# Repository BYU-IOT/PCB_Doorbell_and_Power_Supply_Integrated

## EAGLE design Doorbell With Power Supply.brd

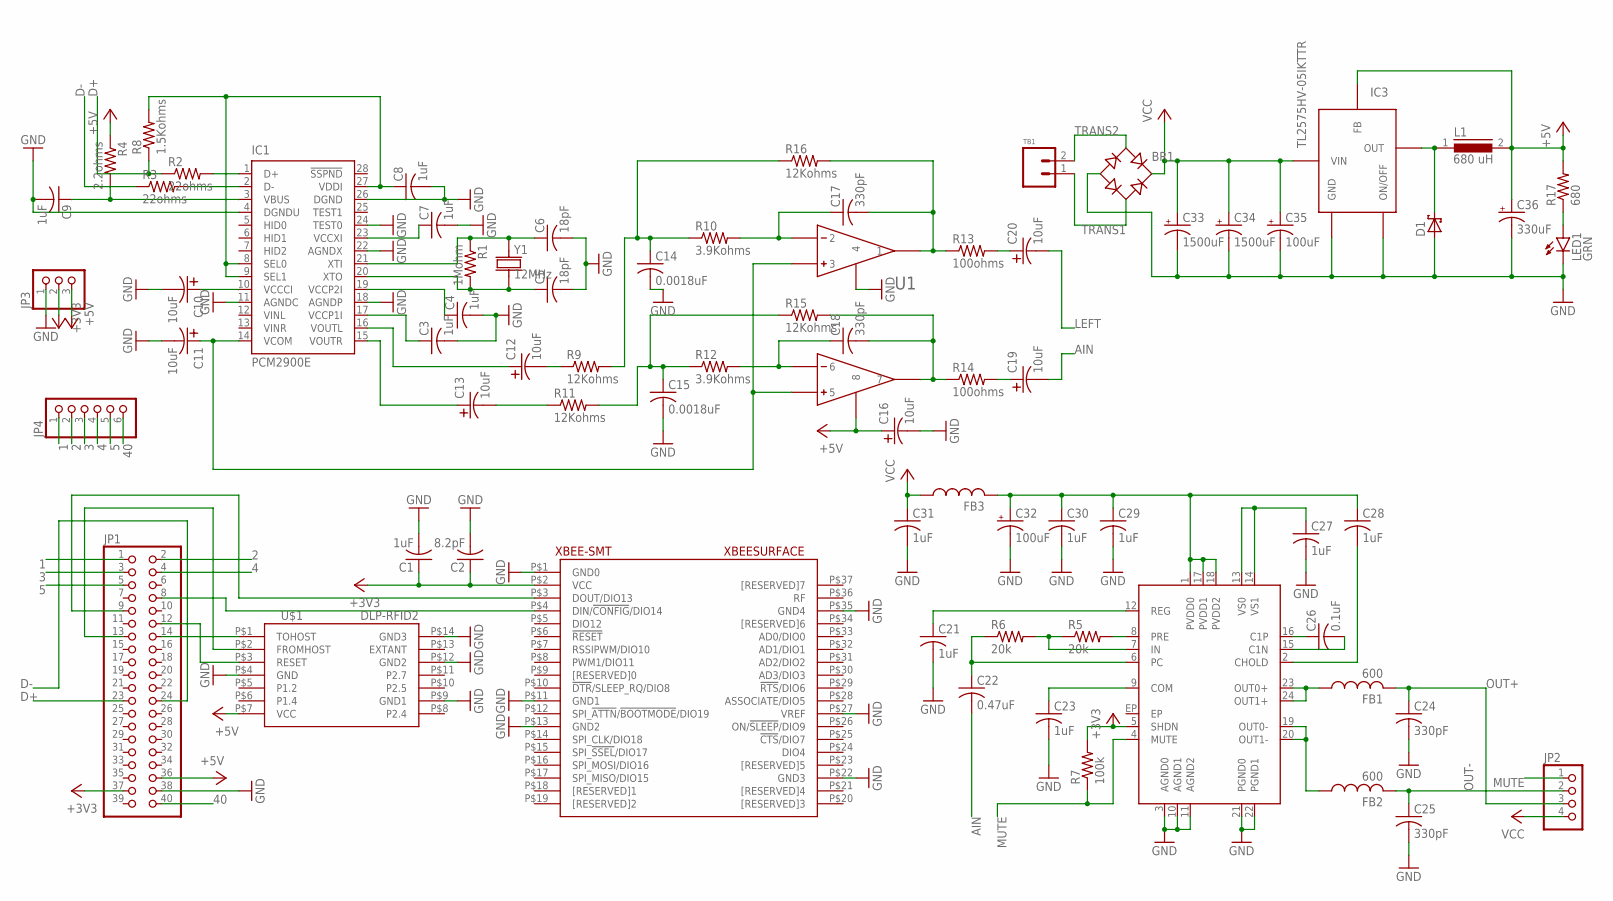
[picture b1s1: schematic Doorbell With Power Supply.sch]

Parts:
BR1: BR; DFS
C1, C3, C4, C7, C8, C9, C21, C23, C27, C28, C29, C30, C31: 1uF; 0603_CAP
C2: 8.2pF; 0603_CAP
C5, C6: 18pF; 0603_CAP
C10, C11, C12, C13, C16, C19, C20: 10uF; 1411_CAP
C14, C15: 0.0018uF; 0603_CAP
C17, C18, C24, C25: 330pF; 0603_CAP
C22: 0.47uF; 0603_CAP
C26: 0.1uF; 0603_CAP
C32, C35: 100uF; F_CAP
C33, C34: 1500uF; J16_CAP
C36: 330uF; F_CAP
D1: SCHOTTKY_DIODE; SMD_DIODE
FB1, FB2: 600; 0805_FB
FB3: FB0805; 0805_FB
IC1: PCM2900E; SSOP28DB
IC2: MAX9737; TQFN24
IC3: TL2575HV-05IKTTR; TO-263-5
JP1: PINHD-2X20; 2X20
JP2: PINHD-1X4; 1X04
JP3: PINHD-1X3; 1X03
JP4: PINHD-1X6; 1X06
L1: 680 uH; DR125
LED1: GRN; 0603_LED
R1: 1Mohm; 0603_RESISTOR
R2, R3: 22ohms; 0603_RESISTOR
R4: 2.2ohms; 0603_RESISTOR
R5, R6: 20k; 0603_RESISTOR
R7: 100k; 0603_RESISTOR
R8: 1.5Kohms; 0603_RESISTOR
R9, R11, R15, R16: 12Kohms; 0603_RESISTOR
R10, R12: 3.9Kohms; 0603_RESISTOR
R13, R14: 100ohms; 0603_RESISTOR
R17: 680; 0603_RESISTOR
TB1: TERMINAL_BLOCK_2
U1: OP-AMP; OPA2353UA
U$1: DLP-RFID2
XBEE-SMT: XBEESURFACE
Y1: 12MHz; CRYSTAL_5X3

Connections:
1: JP1.1, JP4.1
2: JP1.2, JP4.2
3: JP1.3, JP4.3
4: JP1.4, JP4.4
5: JP1.5, JP4.5
40: JP1.40, JP4.6
+3V3: C1.1, C2.1, IC2.5 (SHDN), JP1.37, JP3.2, R7.2, XBEE-SMT.P$2 (VCC)
+5V: C16.P$1, C36.+, IC3.4 (FB), JP1.36, JP3.3, L1.2, R4.1, R17.2, U1.P$8 (8), U$1.P$7 (VCC)
AIN: C19.P$2, C22.2
D+: JP1.23, R2.1, R8.1
D-: JP1.24, R3.1
GND: BR1.-, C1.2, C2.2, C3.2, C4.2, C5.2, C6.2, C7.2, C8.2, C9.2, C10.P$2, C11.P$2, C14.2, C15.2, C16.P$2, C21.2, C23.2, C24.2, C25.2, C27.2, C29.2, C30.2, C31.2, C32.-, C33.-, C34.-, C35.-, C36.-, D1.A, IC1.4 (DGNDU), IC1.11 (AGNDC), IC1.18 (AGNDP), IC1.22 (AGNDX), IC1.24 (TEST0), IC1.26 (DGND), IC2.3 (AGND0), IC2.10 (AGND1), IC2.11 (AGND2), IC2.21 (PGND0), IC2.22 (PGND1), IC3.3 (GND), IC3.5 (ON/OFF), JP1.38, JP3.1, LED1.C, U1.P$4 (4), U$1.P$4 (GND), U$1.P$9 (GND1), U$1.P$12 (GND2), U$1.P$14 (GND3), XBEE-SMT.P$1 (GND0), XBEE-SMT.P$11 (GND1), XBEE-SMT.P$13 (GND2), XBEE-SMT.P$22 (GND3), XBEE-SMT.P$27 (VREF), XBEE-SMT.P$35 (GND4)
LEFT: C20.P$2
MUTE: IC2.4 (MUTE), JP2.1, R7.1
unnamed: JP1.14, U$1.P$1 (TOHOST)
unnamed: IC2.8 (PRE), R5.2
unnamed: IC2.7 (IN), R5.1, R6.2
unnamed: JP1.12, U$1.P$3 (RESET)
unnamed: JP1.13, U$1.P$2 (FROMHOST)
unnamed: JP1.8, XBEE-SMT.P$4 (DIN/!CONFIG!/DIO14)
unnamed: JP1.9, XBEE-SMT.P$3 (DOUT/DIO13)
unnamed: C3.1, IC1.17 (VCCP1I)
unnamed: IC1.1 (D+), R2.2
unnamed: C22.1, IC2.6 (PC), R6.1
unnamed: C8.1, IC1.8 (SEL0), IC1.9 (SEL1), IC1.27 (VDDI), R8.2
unnamed: IC1.2 (D-), R3.2
unnamed: C21.1, IC2.12 (REG)
unnamed: C7.1, IC1.23 (VCCXI)
unnamed: C6.1, IC1.21 (XTI), R1.1, Y1.1
unnamed: C5.1, IC1.20 (XTO), R1.2, Y1.2
unnamed: C4.1, IC1.19 (VCCP2I)
unnamed: C12.P$2, R9.1
unnamed: C13.P$2, R11.1
unnamed: C17.1, R10.2, U1.P$2 (2)
unnamed: C10.P$1, IC1.10 (VCCCI)
unnamed: C11.P$1, IC1.14 (VCOM), U1.P$3 (3), U1.P$5 (5)
unnamed: C18.1, R12.2, U1.P$6 (6)
unnamed: C12.P$1, IC1.16 (VOUTL)
unnamed: C13.P$1, IC1.15 (VOUTR)
unnamed: C14.1, R9.2, R10.1, R16.1
unnamed: C15.1, R11.2, R12.1, R15.1
unnamed: C17.2, R13.1, R16.2, U1.P$1 (1)
unnamed: C18.2, R14.1, R15.2, U1.P$7 (7)
unnamed: D1.C, IC3.2 (OUT), L1.1
unnamed: C20.P$1, R13.2
unnamed: C19.P$1, R14.2
unnamed: C9.1, IC1.3 (VBUS), R4.2
unnamed: C23.1, IC2.9 (COM)
unnamed: LED1.A, R17.1
unnamed: FB1.1, IC2.23 (OUT0+), IC2.24 (OUT1+)
unnamed: FB2.1, IC2.19 (OUT0-), IC2.20 (OUT1-)
unnamed: C26.1, IC2.16 (C1P)
unnamed: C26.2, IC2.15 (C1N)
unnamed: C28.2, IC2.2 (CHOLD)
unnamed: C28.1, C29.1, C30.1, C32.+, FB3.2, IC2.1 (PVDD0), IC2.17 (PVDD1), IC2.18 (PVDD2)
unnamed: C27.1, IC2.13 (VS0), IC2.14 (VS1)
OUT+: C24.1, FB1.2, JP2.3
OUT-: C25.1, FB2.2, JP2.2
TRANS1: BR1.AC2, TB1.1
TRANS2: BR1.AC1, TB1.2
VCC: BR1.+, C31.1, C33.+, C34.+, C35.+, FB3.1, IC3.1 (VIN), JP2.4

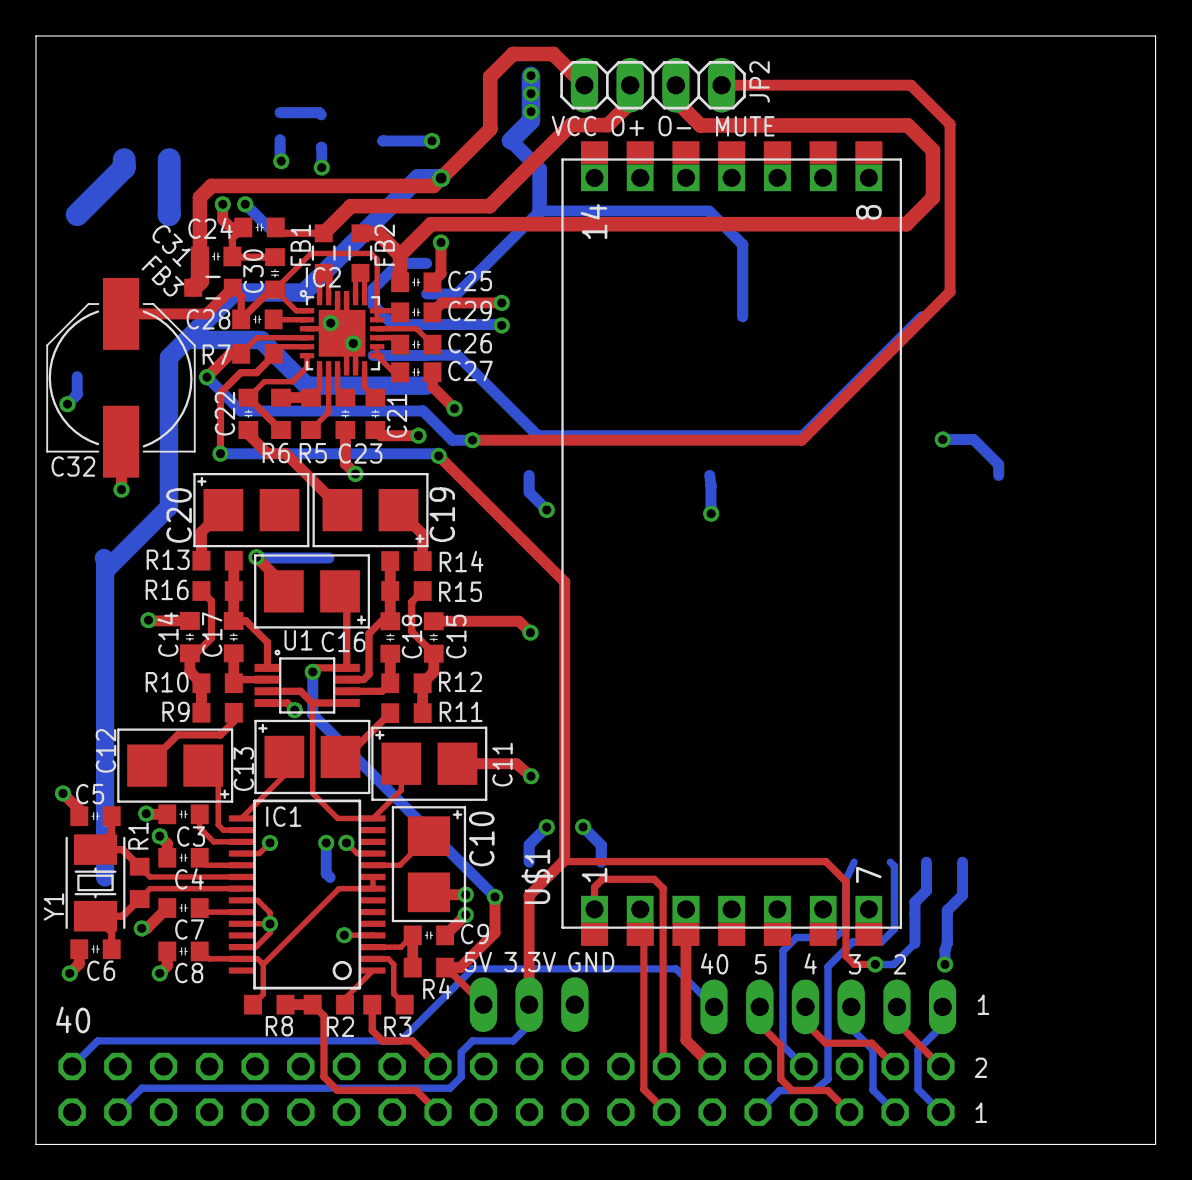
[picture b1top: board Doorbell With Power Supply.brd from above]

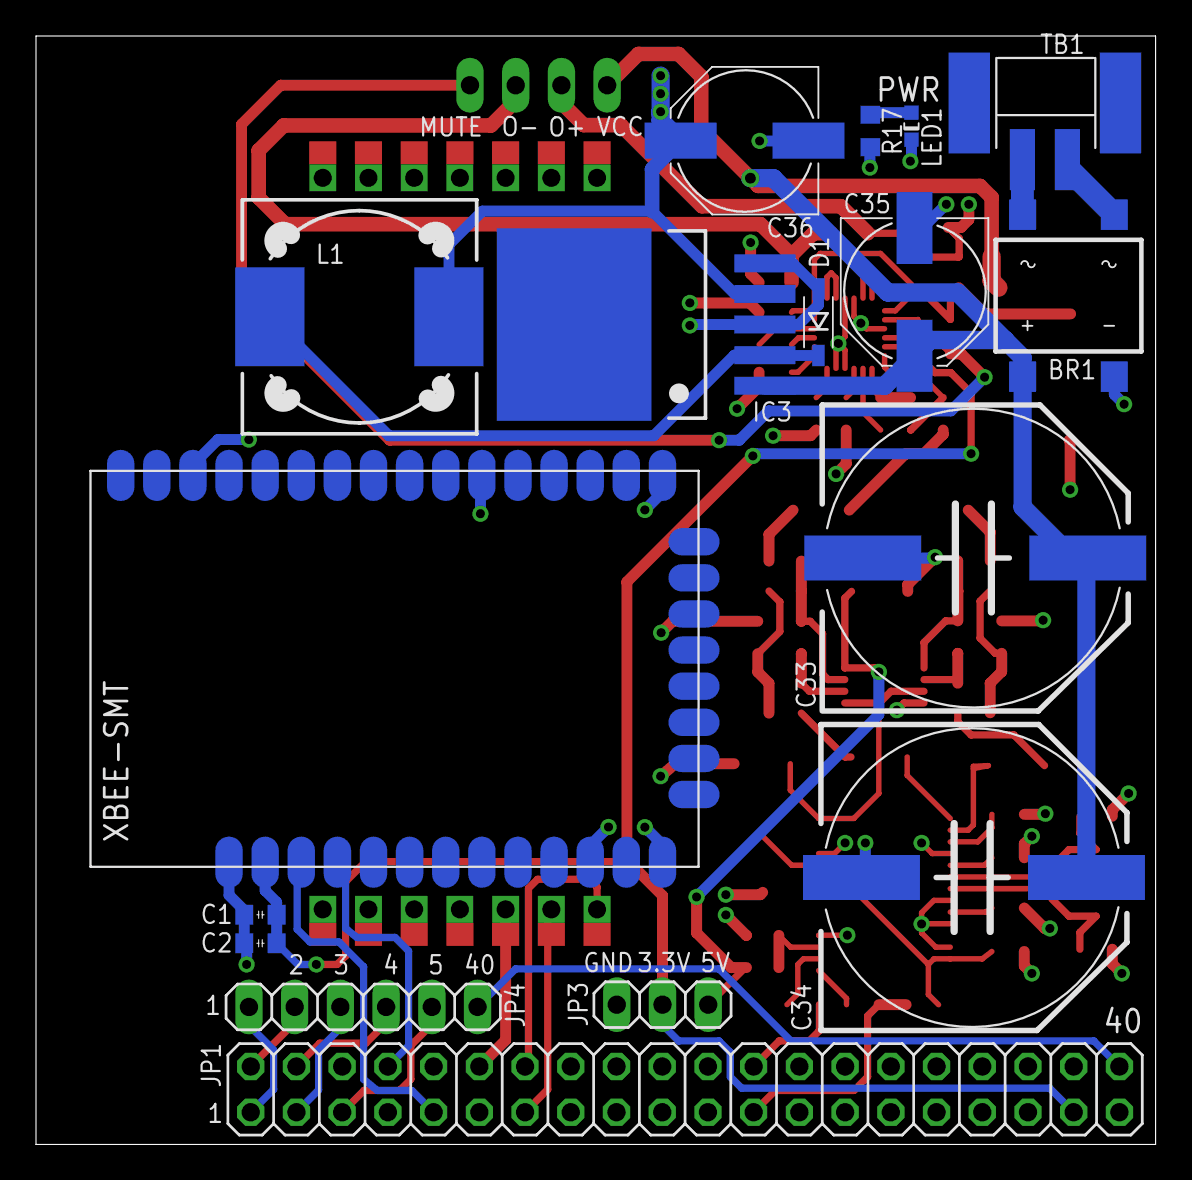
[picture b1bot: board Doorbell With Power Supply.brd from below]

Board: 4 copper layers, 62.2 x 61.6 mm, 72 parts (17 on the bottom side), 60 nets.

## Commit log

2017-05-13 PCB of the Doorbell and power supply board integrated
    This board has yet to be built yet, but this is the first version of
    the power supply and the doorbell coordinator integrated together.
